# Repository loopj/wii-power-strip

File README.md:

<h3 align="center">Slimline PCB to supply power to trimmed Wii motherboards</h3>

## Features

- Solders directly onto the top of a Wii motherboard
- Supplies power to the 1V, 1.15V, 1.8V, and 3.3V points
- Power connector allows for modular builds without soldering/desoldering wires
- Adds pads for the relocation of capacitors (C5, C189, C200) typically removed on more aggressive trims
- Pad for an optional thermistor, for compatibility with [4Layer Technologies RVL-PMS](https://4layertech.com/products/rvl-pms-2)
- Fits entirely within the outline of an Omega trim
- Fits under heatplates/heatsinks

## Parts / Ordering

- Grab the Gerber files for the [latest release](https://github.com/loopj/wii-power-strip/releases/latest)
- Order a 2-layer, 0.6mm PCB from JLCPCB or similar fab
- Purchase a 6-pin Molex Pico-Lock connector, PN 504050-0691 ([DigiKey](https://www.digikey.com/en/products/detail/molex/5040500691/4357148), [Mouser](https://www.mouser.com/ProductDetail/Molex/504050-0691?qs=bvCPb%252BE7ys2K1LQC9e%2FvRg%3D%3D))
- Purchase either a pre-assembled cable, or parts to crimp your own
  - 50mm pre-assembled cable, PN 15132-0600 ([DigiKey](https://www.digikey.com/en/products/detail/molex/0151320600/7423256), [Mouser](https://www.mouser.com/ProductDetail/Molex/15132-0600?qs=HXFqYaX1Q2wQ%2F2lUgfK5Kw%3D%3D))
  - 100mm pre-assembled cable, PN 15132-0601 ([DigiKey](https://www.digikey.com/en/products/detail/molex/0151320601/7423257), [Mouser](https://www.mouser.com/ProductDetail/Molex/15132-0601?qs=HXFqYaX1Q2xvCBLpk4R9sg%3D%3D))
  - Connector, PN 504051-0601 ([DigiKey](https://www.digikey.com/en/products/detail/molex/5040510601/4357150), [Mouser](https://www.mouser.com/ProductDetail/Molex/504051-0601?qs=bvCPb%252BE7ys2KoBFgs2%2FzNw%3D%3D))
  - Crimp terminals, PN 504052-0098 ([DigiKey](https://www.digikey.com/en/products/detail/molex/5040520098/4357152), [Mouser](https://www.mouser.com/ProductDetail/Molex/504052-0098-Cut-Strip?qs=lzT3SgJKZn3tXLBIQ9V4FQ%3D%3D))
- Optional - 10KΩ thermistor with a 3380K B value, in an 0603 SMD package

## Installation

- If you are doing a motherboard trim that will trim off C5 or C189, desolder these and save them
- If you are doing a NAND relocation which removes C200, desolder this and save it
- Solder the connector and any rescued capacitors to the board by hand or using a hot plate
- Place board on the Wii motherboard, it should self-align
- Solder the pads on the edge of the board to the Wii motherboard
  - 1V0 to the top of C143
  - 1V15 to the left of C17
  - 1V8 to the via array at the top left. You may wish to scratch away some solder mask to have more copper to solder to.
  - 3V3 to the top of C128
  - GND to the bottom of C180 and C143
- Use plenty of solder and flux!

## C189 height

Some motherboard revisions have a very tall (~2.9mm) C189 capacitor, which can interfere with heatplates if you are relocating it. If you have one of these boards, you may wish to consider purchasing a lower profile capacitor. As long as it is a 220uF, 6.3V+, 2917 or 2312 SMD package capacitor it should work fine. The Kyocera AVX NOJY227M006RWJ is a low profile version of the original cap used on the Wii. The TAJX227K006RNJ or TAJY227K006RNJ should also both work.

## RVL-PMS Companion Board

If you want to use Power Strip with the 4Layer Technologies [RVL-PMS-2](https://4layertech.com/products/rvl-pms-2), or [RVL-PMS-Lite](https://4layertech.com/products/pms2-lite) boards, [Y2K](https://github.com/y2k-x) has kindly designed a carrier board called the *Power Strip PMS Companion*, which is included in this repository for convenience.

You can read more about it in the [pms-companion](pms-companion) directory.

## License

Permissively released under the Solderpad Hardware License v2.1

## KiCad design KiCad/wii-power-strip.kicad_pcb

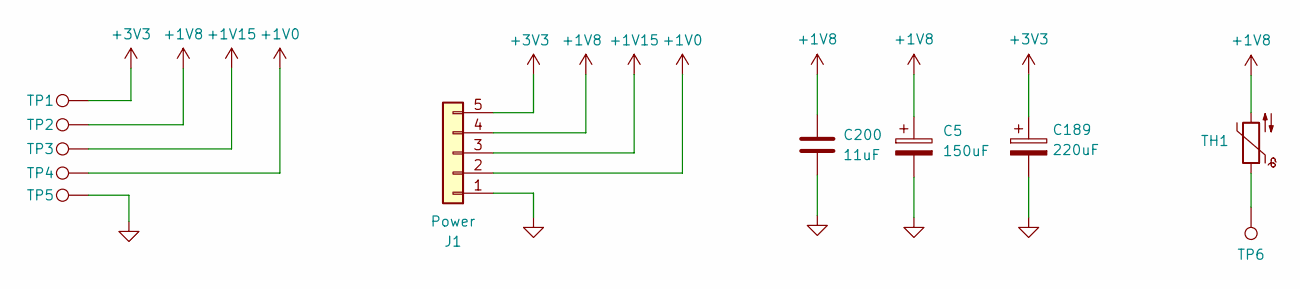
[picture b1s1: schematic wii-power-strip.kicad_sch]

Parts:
C5: 150uF; CP_EIA-7343-20_Kemet-V
C189: 220uF; CP_EIA-7343-20_Kemet-V
C200: 11uF
J1: Power; 5040500591
TH1: Thermistor_NTC; R_0603_1608Metric
TP1: 3V3; TestPoint_Pad_1.5x1.0mm
TP2: 1V8; TestPoint_Pad_3x1.0mm
TP3: 1V15; TestPoint_Pad_3x1.0mm
TP4: 1V0; TestPoint_Pad_3x1.0mm
TP5: GND; TestPoint_Pad_3x1.0mm
TP6: T-; TestPoint_Pad_D1.0mm

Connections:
+1V0: J1.2, TP4.1
+1V8: C5.1, C200.1, J1.4, TH1.2, TP2.1
+1V15: J1.3, TP3.1
+3V3: C189.1, J1.5, TP1.1
GND: C5.2, C189.2, C200.2, J1.1, TP5.1
unnamed: TH1.1, TP6.1

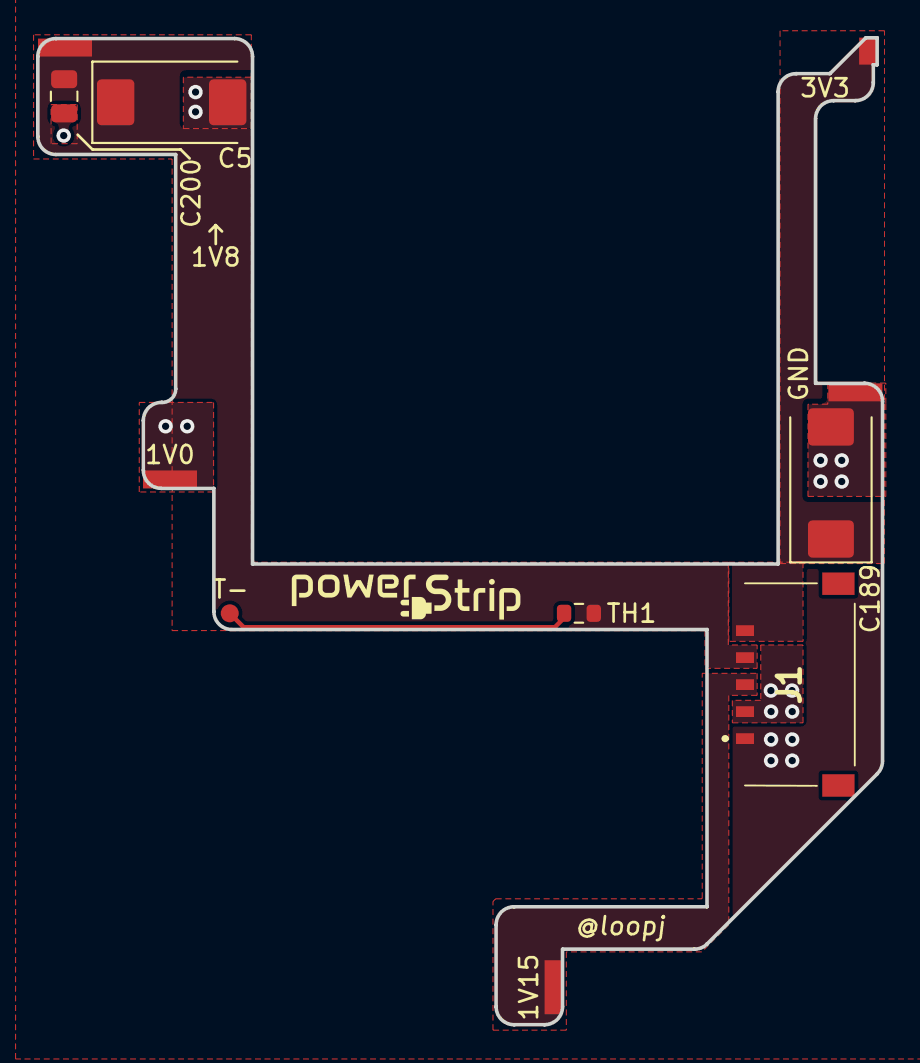
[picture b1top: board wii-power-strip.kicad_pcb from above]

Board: 2 copper layers, 46.9 x 54.8 mm, 11 parts (0 on the bottom side), 6 nets.

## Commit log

2024-03-04 Add missing logo images
2024-03-04 Add power strip render with logo
2024-03-04 Link to gerber zip from README
2024-03-04 Add license info to README
2024-03-04 Note about C189
2024-03-04 Update README wording
2024-03-04 Alternative low profile caps
2024-03-05 Left facing, 6-pin power connector
2024-03-06 Update README for r2
2024-03-27 Fix clearance issue with connector and cap
2024-03-27 Add dxf of full outline in case people want to make custom outlines
2024-04-11 Add pms companion to repo
2024-04-11 Add README, restructure
2024-04-11 Minor readme edit
2024-04-11 Fix 3d model references
2024-04-11 Update profile links
2024-05-10 Add castellated edges to voltage connections
